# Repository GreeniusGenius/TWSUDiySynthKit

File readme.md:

# About

- This product is borne out of an original synthesiser kit built by the now bankrupt [Tech Will Save Us](https://en.wikipedia.org/wiki/Technology_Will_Save_Us) company.
- The solderless breadboard nature of it frustrated me, and the lack of room to add a microcontroller for MIDI functionality on the breadboard made it unusable for how I would wish to use it.
- Then I got bored whilst designing it, and decided I'd turn it into a Pi Pico (2(W)) dev board too.
- That way I can prototype all of my projects in a single multipurpose board.
- It supports a Raspberry Pi standard hat.
- It supports a Raspberry Pi Pico bonnet.
- _The second Pi you see in the renderings is actually where two headers will go allowing bonnets to be attached like eInk displays_
- It supports Adafruit Stemma QT and Stemma connectors - which are perfect for prototyping using breakout boards due to the reliable solderless connections.
- It lets me try out the usage of jumpers to bypass voltage dividers reducing potential PCB revisions required due to calculation errors.

_The PCB is a cost-effective two layer design with ground pours and high density of via stitching reduce ground loops and EMI._

_Plated and grounded mounting holes are used to allow easy multimeter probing and increase durability._

_The case shields the synthesiser board and Pi Pico (2(W)) whilst the bonnet, hat, and JST connectors for peripherals are easily accessible_

## Bill of Materials
| Reference | Qty | Value                                             | Datasheet                                                                                                                                                                                                                                                                                                                                                                                                                                                                      | Link / URL                                                                                                     | Manufacturer  | Manufacturer_Part_Number | Price (GBP) | GBP/USD              | Price (USD) | Justification                                                                                            |
| --------- | --- | ------------------------------------------------- | ------------------------------------------------------------------------------------------------------------------------------------------------------------------------------------------------------------------------------------------------------------------------------------------------------------------------------------------------------------------------------------------------------------------------------------------------------------------------------ | -------------------------------------------------------------------------------------------------------------- | ------------- | ------------------------ | ----------- | -------------------- | ----------- | -------------------------------------------------------------------------------------------------------- |
| R1, R2    | 2   | 2k 16mm Potentiometer                             | [https://static.rapidonline.com/pdf/65-1480.pdf](https://static.rapidonline.com/pdf/65-1480.pdf)                                                                                                                                                                                                                                                                                                                                                                               | https://www.rapidonline.com/omeg-eco2k2lin-2k2-linear-single-16mm-control-pot-65-1401                          | Omeg          | ECO2K2LIN                | £1.75       |  $              1.36 | USD 2.38    | For the volume control and adjustment of the midi volume too                                             |
| R3, R6    | 2   | 470k 16mm potentiometer                           | [https://static.rapidonline.com/pdf/65-1400e.pdf](https://static.rapidonline.com/pdf/65-1400e.pdf)                                                                                                                                                                                                                                                                                                                                                                             | https://www.rapidonline.com/omeg-ecoswx470klin-470k-eco-16mm-linear-switched-control-65-1494                   | Omeg          | ECOSWX470KLIN            | £2.57       |  $              1.36 | USD 3.49    | For the input for the synthesizer                                                                        |
| J6        | 1   | JST XH p2.54mm 4 pin 20cm long wire and connector | [https://www.aliexpress.com/item/1005007460897865.html#nav-specification](https://www.aliexpress.com/item/1005007460897865.html#nav-specification)                                                                                                                                                                                                                                                                                                                             | [https://www.aliexpress.com/item/1005007460897865.html](https://www.aliexpress.com/item/1005007460897865.html) | Generic       | ~                        | £0.75       |  $              1.36 | USD 1.02    | Cables for the PCB mount JST connectors to attach accessories                                            |
| J8        | 1   |  JST SH 1.0mm 4 pin 300mm wire and conenctor      | https://www.aliexpress.com/item/1005007218127653.html?spm=a2g0o.productlist.main.1.63d76305UmTvS8&algo_pvid=8017bda6-71a1-4b7b-932a-028b233ec6b2&algo_exp_id=8017bda6-71a1-4b7b-932a-028b233ec6b2-0&pdp_ext_f=%7B%22order%22%3A%221971%22%2C%22eval%22%3A%221%22%7D&pdp_npi=4%40dis%21GBP%210.59%210.59%21%21%215.53%215.53%21%40210390c917491563321605448e615d%2112000039871029577%21sea%21UK%210%21ABX&curPageLogUid=Gzq5NMQj9i6H&utparam-url=scene%3Asearch%7Cquery_from%3A | https://www.aliexpress.com/item/1005007218127653.html                                                          | Generic       | ~                        | £0.81       |  $              1.36 | USD 2.21    |                                                                                                          |
| J7        | 1   | JST PH 2.0mm 4 pin connector                      | https://www.aliexpress.com/item/32959854422.html#nav-description                                                                                                                                                                                                                                                                                                                                                                                                               | https://www.aliexpress.com/item/32959854422.html                                                               | Generic       | ~                        | £1.63       |  $              1.36 | USD 1.91    |                                                                                                          |
| J8        | 2   | JST PH 2.0mm 3 pin connector                      | https://www.aliexpress.com/item/32959854422.html#nav-description                                                                                                                                                                                                                                                                                                                                                                                                               | https://www.aliexpress.com/item/32959854422.html                                                               | Generic       | ~                        | £1.41       |  $              1.36 | USD 1.91    |                                                                                                          |
| J2        | 1   | JST XH p2.54mm 2 pin 20cm long wire and connector | [https://www.aliexpress.com/item/1005007460897865.html#nav-specification](https://www.aliexpress.com/item/1005007460897865.html#nav-specification)                                                                                                                                                                                                                                                                                                                             | [https://www.aliexpress.com/item/1005007460897865.html](https://www.aliexpress.com/item/1005007460897865.html) | Generic       | ~                        | £0.75       |  $              1.36 | USD 1.02    |                                                                                                          |
| J6        | 1   | 16mm 3V LED Button                                | [https://www.aliexpress.com/item/1005008024309525.html#nav-specification](https://www.aliexpress.com/item/1005008024309525.html#nav-specification)                                                                                                                                                                                                                                                                                                                             | https://www.aliexpress.com/item/1005008024309525.html                                                          | Generic       | ~                        | £1.26       |  $              1.36 | USD 1.71    | Push to pair bluetooth                                                                                   |
|           |     | USB-A to Micro-USB cable 0.9m                     | https://www.amazon.co.uk/dp/B0711PVX6Z?th=1                                                                                                                                                                                                                                                                                                                                                                                                                                    | https://www.amazon.co.uk/dp/B0711PVX6Z                                                                         | Amazon Basics | ~                        | £3.16       |  $              1.36 | USD 4.29    | Genuinely run out of Micro USB cables - happy to find a cheaper one if necessary as long as it does data |
| PCB       | 1   | 5 PCBs (minimum JLCPCB order)                     | ~                                                                                                                                                                                                                                                                                                                                                                                                                                                                              | jlcpcb.com                                                                                                     | JLCPCB        | ~                        | £23.35      |  $              1.36 | USD 31.71   | The PCB                                                                                                  |
|           |     |                                                   |                                                                                                                                                                                                                                                                                                                                                                                                                                                                                |                                                                                                                |               |                          |             |                      |             |                                                                                                          |
|           |     |                                                   |                                                                                                                                                                                                                                                                                                                                                                                                                                                                                |                                                                                                                |               |                          |             |                      |             |                                                                                                          |
|           |     |                                                   |                                                                                                                                                                                                                                                                                                                                                                                                                                                                                |                                                                                                                |               |                          |             |                      |             |                                                                                                          |
|           |     |                                                   |                                                                                                                                                                                                                                                                                                                                                                                                                                                                                |                                                                                                                |               | Total Price              | £37.44      |                      | USD 51.65   |                                                                                                          |
| **Reference**                    | **Qty** | **Value**                    | **DNP** | **Exclude from BOM** | **Exclude from Board** | **Footprint**                                                    | **Datasheet**                                                                                                                                                                                                                                                                  | **JLCPCB ID** | **Manufacturer**                      | **Manufacturer_Part_Number** | **Mouser Part Number** |
| -------------------------------- | ------- | ---------------------------- | ------- | -------------------- | ---------------------- | ---------------------------------------------------------------- | ------------------------------------------------------------------------------------------------------------------------------------------------------------------------------------------------------------------------------------------------------------------------------ | ------------- | ------------------------------------- | ---------------------------- | ---------------------- |
| **R5**                           | 1       | 2k_0603                      |         |                      |                        | PCM_Resistor_SMD_AKL:R_0603_1608Metric_Pad0.98x0.95mm_HandSolder | [https://www.vishay.com/doc?60018](https://www.vishay.com/doc?60018)                                                                                                                                                                                                           | C2076992      | Vishay                                | M55342E12B2B00RT5            | 75-M55342E12B2B00RT5   |
| **R8,R9**                        | 2       | 10k_0603                     |         |                      |                        | PCM_Resistor_SMD_AKL:R_0603_1608Metric_Pad0.98x0.95mm_HandSolder | [https://www.vishay.com/doc?28758](https://www.vishay.com/doc?28758)                                                                                                                                                                                                           | C2130614      | Vishay                                | TNPW060310K0FHEA             | 71-TNPW060310K0FHEA    |
| **R4,R7**                        | 2       | 1k_0603                      |         |                      |                        | PCM_Resistor_SMD_AKL:R_0603_1608Metric_Pad1.05x0.95mm_HandSolder | [https://www.mouser.co.uk/datasheet/2/385/SEI_RMCF_RMCP-3077565.pdf](https://www.mouser.co.uk/datasheet/2/385/SEI_RMCF_RMCP-3077565.pdf)                                                                                                                                       | C4130738      | SEI Stackpole                         | RMCF0603JG1K00               | 708-RMCF0603JG1K00     |
| **R13**                          | 1       | 1k_1210                      |         |                      |                        | PCM_Resistor_SMD_AKL:R_0603_1608Metric_Pad1.05x0.95mm_HandSolder | [https://4donline.ihs.com/images/VipMasterIC/IC/PANA/PANA-S-A0012789169/PANA-S-A0012789169-1.pdf?hkey=CECEF36DEECDED6468708AAF2E19C0C6](https://4donline.ihs.com/images/VipMasterIC/IC/PANA/PANA-S-A0012789169/PANA-S-A0012789169-1.pdf?hkey=CECEF36DEECDED6468708AAF2E19C0C6) | C20024203     | Yageo                                 | ERJ-T14LK102U                | 667-ERJ-T14LK102U      |
| **C7**                           | 1       | 10uf Electrolytic Capacitor  |         |                      |                        | PCM_Capacitor_THT_AKL:CP_Radial_D6.3mm_P2.50mm                   | [https://industrial.panasonic.com/cdbs/www-data/pdf/RDF0000/ABA0000C1059.pdf](https://industrial.panasonic.com/cdbs/www-data/pdf/RDF0000/ABA0000C1059.pdf)                                                                                                                     | C1583769      | Panasonic                             | ECE-A1HKS100B                | 667-ECE-A1HKS100B      |
| **R12**                          | 1       | 68R_1210                     |         |                      |                        | PCM_Resistor_SMD_AKL:R_0603_1608Metric_Pad1.05x0.95mm_HandSolder | [https://www.mouser.co.uk/datasheet/2/447/PYu_AC_51_RoHS_L_11-3418659.pdf](https://www.mouser.co.uk/datasheet/2/447/PYu_AC_51_RoHS_L_11-3418659.pdf)                                                                                                                           | C230487       | Yageo                                 | AC1210JR-0768RL              | 603-AC1210JR-0768RL    |
| **U1**                           | 1       | NE556                        |         |                      |                        | Package_DIP:DIP-14_W7.62mm_Socket_LongPads                       | [http://www.ti.com/lit/ds/symlink/ne556.pdf](http://www.ti.com/lit/ds/symlink/ne556.pdf)                                                                                                                                                                                       | C66175        | Texas Instruments                     | NE556N                       | 595-NE556N             |
| **A1**                           | 1       | RaspberryPi_Pico_2W          |         |                      |                        | Module_RaspberryPi_Pico:RaspberryPi_Pico_W_SMD                   | [https://datasheets.raspberrypi.com/picow/pico-2-w-datasheet.pdf](https://datasheets.raspberrypi.com/picow/pico-2-w-datasheet.pdf)                                                                                                                                             |               | Raspberry Pi Foundation               | SC1633                       | 358-SC1633             |
| **J8**                           | 1       | Conn_01x04_Socket            |         |                      |                        | Connector_JST:JST_SH_SM04B-SRSS-TB_1x04-1MP_P1.00mm_Horizontal   | [https://www.mouser.co.uk/datasheet/2/564/eGH-3477624.pdf](https://www.mouser.co.uk/datasheet/2/564/eGH-3477624.pdf)                                                                                                                                                           | C7279904      | Japan Solderless Terminals            | SM04B-GHMG-TB-(LF)(SN)       | 306-SM04BGHMGTBLFSN    |
| **J6**                           | 1       | Conn_01x04_Socket            |         |                      |                        | Connector_JST:JST_XH_S4B-XH-A-1_1x04_P2.50mm_Horizontal          | [https://www.mouser.co.uk/datasheet/2/564/eXH-3476786.pdf](https://www.mouser.co.uk/datasheet/2/564/eXH-3476786.pdf)                                                                                                                                                           | C163037       | Japan Solderless Terminals            | S4B-XH-A-1(LF)(SN)           | 306-S4BXHA1LFSN        |
| **R3,R6**                        | 2       | ECO2K2LIN                    |         |                      |                        | Connector_JST:JST_XH_S3B-XH-A-1_1x03_P2.50mm_Horizontal          | [https://static.rapidonline.com/pdf/65-1400e.pdf](https://static.rapidonline.com/pdf/65-1400e.pdf), [https://www.mouser.co.uk/datasheet/2/564/eXH-3476786.pdf](https://www.mouser.co.uk/datasheet/2/564/eXH-3476786.pdf)                                                       | C163036       | Japan Solderless Terminals            | S3B-XH-A-1(LF)(SN)           | 306-S3BXHA1LFSN        |
| **R1,R2**                        | 2       | ECOSWX470KLIN                |         |                      |                        | Connector_JST:JST_XH_S3B-XH-A-1_1x03_P2.50mm_Horizontal          | [https://static.rapidonline.com/pdf/65-1494.pdf](https://static.rapidonline.com/pdf/65-1494.pdf), [https://www.mouser.co.uk/datasheet/2/564/eXH-3476786.pdf](https://www.mouser.co.uk/datasheet/2/564/eXH-3476786.pdf)                                                         | C163036       | Japan Solderless Terminals            | S3B-XH-A-1(LF)(SN)           | 306-S3BXHA1LFSN        |
| **J7**                           | 1       | Conn_01x04_Socket            |         |                      |                        | Connector_JST:JST_PH_S4B-PH-K_1x04_P2.00mm_Horizontal            | [https://www.mouser.co.uk/datasheet/2/564/JST_B4B_PH_SM4_TB_LF_SN_ePH-3481264.pdf](https://www.mouser.co.uk/datasheet/2/564/JST_B4B_PH_SM4_TB_LF_SN_ePH-3481264.pdf)                                                                                                           | C157926       | Japan Solderless Terminals            | S4B-PH-K-S(LF)(SN)           | 306-S4BPHKSLFSN        |
| **J9,J10**                       | 2       | Conn_01x03_Socket            |         |                      |                        | Connector_JST:JST_PH_S3B-PH-K_1x03_P2.00mm_Horizontal            | [https://www.mouser.co.uk/datasheet/2/564/JST_B4B_PH_SM4_TB_LF_SN_ePH-3481264.pdf](https://www.mouser.co.uk/datasheet/2/564/JST_B4B_PH_SM4_TB_LF_SN_ePH-3481264.pdf)                                                                                                           | C157929       | Japan Solderless Terminals Commercial | S3B-PH-K-S(LF)(SN)           | 306-S3BPHKSLFSN        |
| **J2**                           | 1       | Conn_01x02                   |         |                      |                        | Connector_JST:JST_XH_S2B-XH-A-1_1x02_P2.50mm_Horizontal          | [https://www.mouser.co.uk/datasheet/2/564/eXH-3476786.pdf](https://www.mouser.co.uk/datasheet/2/564/eXH-3476786.pdf)                                                                                                                                                           | C157931       | Japan Solderless Terminals            | S2B-XH-A(LF)(SN)             | 306-S2B-XH-ALFSN       |
| **C4,C5,C6**                     | 3       | 0.1uF_0603_16V               |         |                      |                        | Capacitor_SMD:C_1206_3216Metric_Pad1.33x1.80mm_HandSolder        | [https://www.mouser.co.uk/datasheet/2/585/MLCC-1837944.pdf](https://www.mouser.co.uk/datasheet/2/585/MLCC-1837944.pdf)                                                                                                                                                         | C6766062      | Samsung Electro-Mechanics             | CL31B104KBCNNND              | 187-CL31B104KBCNNND    |
| **C1,C3,C9,C10,C11,C12,C13,C14** | 8       | 0.1uF                        |         |                      |                        | Capacitor_SMD:C_1206_3216Metric_Pad1.33x1.80mm_HandSolder        | [https://www.mouser.co.uk/datasheet/2/585/MLCC-1837944.pdf](https://www.mouser.co.uk/datasheet/2/585/MLCC-1837944.pdf)                                                                                                                                                         | C6766062      | Samsung Electro-Mechanics             | CL31B104KBCNNND              | 187-CL31B104KBCNNND    |
| **C2,C8**                        | 2       | 10nF_0603_25V                |         |                      |                        | Capacitor_SMD:C_1206_3216Metric_Pad1.33x1.80mm_HandSolder        | [https://www.mouser.co.uk/datasheet/2/585/MLCC-1837944.pdf](https://www.mouser.co.uk/datasheet/2/585/MLCC-1837944.pdf)                                                                                                                                                         | C16196152     | Samsung Electro-Mechanics             | CL31B103KHFNFNE              | 187-CL31B103KHFNFNE    |
| **TP1,TP2**                      | 2       | TestPoint                    |         |                      |                        | TestPoint:TestPoint_Pad_D2.5mm                                   | ~                                                                                                                                                                                                                                                                              |               |                                       |                              |                        |
| **NT1,NT2,NT3**                  | 3       | NetTie_2                     |         | Excluded from BOM    |                        | NetTie:NetTie-2_SMD_Pad0.5mm                                     | ~                                                                                                                                                                                                                                                                              |               |                                       |                              |                        |
| **J14**                          | 1       | Conn_01x04_Socket            |         |                      |                        | Connector_PinSocket_2.54mm:PinSocket_1x04_P2.54mm_Vertical       | ~                                                                                                                                                                                                                                                                              |               |                                       |                              |                        |
| **J11,J12**                      | 2       | Conn_01x03_Socket            |         |                      |                        | Connector_PinSocket_2.54mm:PinSocket_1x03_P2.54mm_Vertical       | ~                                                                                                                                                                                                                                                                              |               |                                       |                              |                        |
| **J5**                           | 1       | Raspberry_Pi_2x20_PTH        |         |                      |                        | Connector_PinHeader_2.54mm:PinHeader_2x20_P2.54mm_Vertical       | [https://www.raspberrypi.org/documentation/hardware/raspberrypi/schematics/rpi_SCH_3bplus_1p0_reduced.pdf](https://www.raspberrypi.org/documentation/hardware/raspberrypi/schematics/rpi_SCH_3bplus_1p0_reduced.pdf)                                                           |               |                                       |                              |                        |
| **J3,J4**                        | 2       | Conn_01x07_Pin               |         |                      |                        | Connector_PinSocket_2.54mm:PinSocket_1x07_P2.54mm_Horizontal     | ~                                                                                                                                                                                                                                                                              |               |                                       |                              |                        |
| **J1**                           | 1       | Conn_02x02_Counter_Clockwise |         |                      |                        | Connector_PinSocket_2.54mm:PinSocket_2x02_P2.54mm_Horizontal     | ~                                                                                                                                                                                                                                                                              |               |                                       |                              |                        |
| **H5,H6,H7,H8,H9,H10,H11,H12**   | 8       | MountingHole_Pad             |         | Excluded from BOM    |                        | MountingHole:MountingHole_2.7mm_M2.5_DIN965_Pad                  | ~                                                                                                                                                                                                                                                                              |               |                                       |                              |                        |
| **H1,H2,H3,H4**                  | 4       | MountingHole_Pad             |         | Excluded from BOM    |                        | MountingHole:MountingHole_2.2mm_M2_DIN965                        | ~                                                                                                                                                                                                                                                                              |               |                                       |                              |                        |
| **A2**                           | 1       | RaspberryPi_Pico_W           |         | Excluded from BOM    |                        | Module_RaspberryPi_Pico:RaspberryPi_Pico_Common_MountingHoles    | [https://datasheets.raspberrypi.com/picow/pico-w-datasheet.pdf](https://datasheets.raspberrypi.com/picow/pico-w-datasheet.pdf)                                                                                                                                                 |               |                                       |                              |                        |

| FileName                   | Quantity | Price  |
|----------------------------|----------|--------|
| InitialBaseBoard Base.step | 1        | $17.16 |
| InitialBaseBoard Lid.step  | 1        | $7.78  |

Notes: The .csv file contains the PCB mounted bill of materials.
The ExtraBOM contains the wiring needed to connect etc.
The link to the mouser basket is here: https://www.mouser.co.uk/ProjectManager/ProjectDetail.aspx?AccessID=711d47ef2e

Mouser components + shipping to United Kingdom is £24.41 or US$33.12

Components in .xlsx are £43.17 or US$59.46

3D Printed Casing is about US$24.94 (£18.41) + at least US$16.10 (£11.88) shipping from PCBWay for a total of £30.29 and US$41.04

**Therefore the total cost is £97.87 and US$133.62.**

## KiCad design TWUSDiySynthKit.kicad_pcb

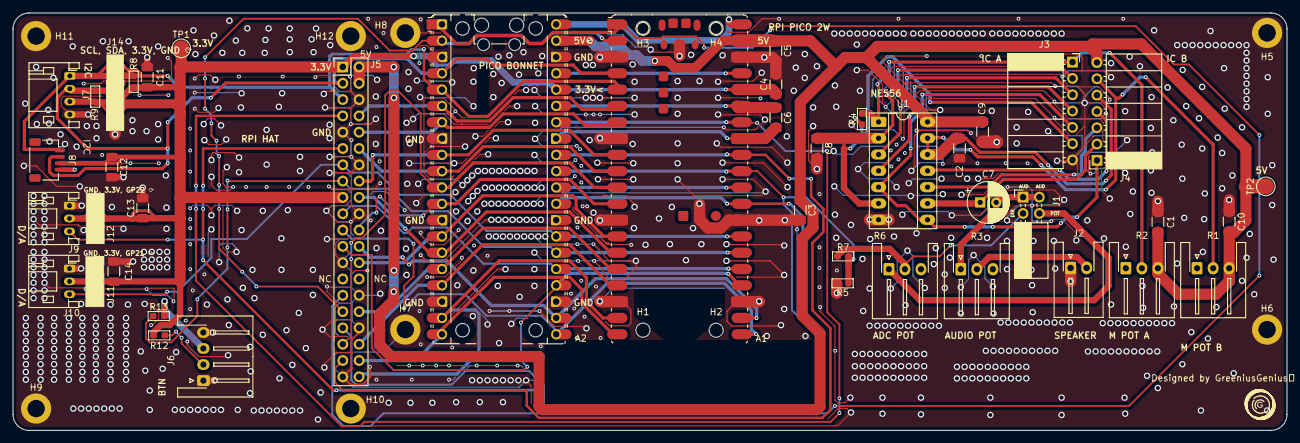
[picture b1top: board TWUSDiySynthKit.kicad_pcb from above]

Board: 2 copper layers, 198.4 x 65.0 mm, 58 parts (0 on the bottom side), 52 nets.

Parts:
A1: RaspberryPi_Pico_W; RaspberryPi_Pico_W_SMD
A2: RaspberryPi_Pico_W; RaspberryPi_Pico_Common_MountingHoles
C1, C3, C9, C10, C11, C12, C13, C14: 0.1uF; C_1206_3216Metric_Pad1.33x1.80mm_HandSolder
C2, C8: 10nF_0603_25V; C_1206_3216Metric_Pad1.33x1.80mm_HandSolder
C4, C5, C6: 0.1uF_0603_16V; C_1206_3216Metric_Pad1.33x1.80mm_HandSolder
C7: 10uf Electrolytic Capacitor; CP_Radial_D6.3mm_P2.50mm
H1, H2, H3, H4: MountingHole_Pad; MountingHole_2.2mm_M2_DIN965
H5, H6, H7, H8, H9, H10, H11, H12: MountingHole_Pad; MountingHole_2.7mm_M2.5_DIN965_Pad
J1: Conn_02x02_Counter_Clockwise; PinSocket_2x02_P2.54mm_Horizontal
J2: Conn_01x02; JST_XH_S2B-XH-A-1_1x02_P2.50mm_Horizontal
J3, J4: Conn_01x07_Pin; PinSocket_1x07_P2.54mm_Horizontal
J5: Raspberry_Pi_2x20_PTH; PinHeader_2x20_P2.54mm_Vertical
J6: Conn_01x04_Socket; JST_XH_S4B-XH-A-1_1x04_P2.50mm_Horizontal
J7: Conn_01x04_Socket; JST_PH_S4B-PH-K_1x04_P2.00mm_Horizontal
J8: Conn_01x04_Socket; JST_SH_SM04B-SRSS-TB_1x04-1MP_P1.00mm_Horizontal
J9, J10: Conn_01x03_Socket; JST_PH_S3B-PH-K_1x03_P2.00mm_Horizontal
J11, J12: Conn_01x03_Socket; PinSocket_1x03_P2.54mm_Vertical
J14: Conn_01x04_Socket; PinSocket_1x04_P2.54mm_Vertical
NT1, NT2, NT3: NetTie_2; NetTie-2_SMD_Pad0.5mm
R1, R2: ECOSWX470KLIN; JST_XH_S3B-XH-A-1_1x03_P2.50mm_Horizontal
R3, R6: ECO2K2LIN; JST_XH_S3B-XH-A-1_1x03_P2.50mm_Horizontal
R4, R7: 1k_0603; R_0603_1608Metric_Pad1.05x0.95mm_HandSolder
R5: 2k_0603; R_0603_1608Metric_Pad0.98x0.95mm_HandSolder
R8, R9: 10k_0603; R_0603_1608Metric_Pad0.98x0.95mm_HandSolder
R12: 68R_1210; R_0603_1608Metric_Pad1.05x0.95mm_HandSolder
R13: 1k_1210; R_0603_1608Metric_Pad1.05x0.95mm_HandSolder
TP1, TP2: TestPoint; TestPoint_Pad_D2.5mm
U1: NE556; DIP-14_W7.62mm_Socket_LongPads

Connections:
1DIS: J3.1, R2.2 (Wiper), R4.2, U1.1 (DIS)
2THR: C8.1, J3.2, NT2.1, U1.2 (THR)
3CV: J3.3, U1.3 (CV)
4RST: J3.4, U1.4 (R)
5OUT: J3.5, NT3.1, U1.5 (Q)
5V: A1.39 (VSYS), A2.39 (VSYS), C1.1, C3.1, C5.1, C9.1, C10.1, J4.14, J5.2 (5V), J5.4 (5V), R1.3, R2.3, TP2.1, U1.14 (VCC)
6TRIG: J3.6, NT2.2, R4.1, U1.6 (TR)
8TRIG: J4.8, NT3.2, U1.8 (TR)
9OUT: C7.1, J4.9, U1.9 (Q)
10RST: J4.10, U1.10 (R)
11CV: J4.11, U1.11 (CV)
12THR: C2.1, J4.12, NT1.1, U1.12 (THR)
13DIS: J4.13, NT1.2, R1.2 (Wiper), U1.13 (DIS)
+3.3V: A1.36 (3V3), A2.36 (3V3), C4.1, C11.1, C12.1, C13.1, C14.1, J5.1 (3V3), J5.17 (3V3), J7.3, J8.3, J9.2, J10.2, J11.2, J12.2, J14.3, R8.2, R9.2, R12.1, TP1.1
GND: A1.3 (GND), A1.8 (GND), A1.13 (GND), A1.18 (GND), A1.23 (GND), A1.28 (GND), A1.38 (GND), A1.D2 (GND), A1.TP1 (USB_GND), A2.3 (GND), A2.8 (GND), A2.13 (GND), A2.18 (GND), A2.23 (GND), A2.28 (GND), A2.38 (GND), C1.2, C2.2, C3.2, C4.2, C5.2, C8.2, C9.2, C10.2, C11.2, C12.2, C13.2, C14.2, H5.1, H6.1, H7.1, H8.1, H9.1, H10.1, H11.1, H12.1, J2.1, J3.7, J5.6 (GND), J5.9 (GND), J5.14 (GND), J5.20 (GND), J5.25 (GND), J5.30 (GND), J5.34 (GND), J5.39 (GND), J6.1, J6.4, J7.4, J8.4, J9.1, J10.1, J11.1, J12.1, J14.4, R5.2, U1.7 (GND)
unnamed: A1.37 (3V3_EN), A2.37 (3V3_EN)
unnamed: A1.35 (ADC_VREF), A2.35 (ADC_VREF), C6.1
unnamed: A1.33 (AGND), A2.33 (AGND), C6.2
unnamed: A1.1 (GPIO0), A2.1 (GPIO0), J5.29 (GCLK1/GPIO5)
unnamed: A1.2 (GPIO1), A2.2 (GPIO1), J5.31 (GCLK2/GPIO6)
unnamed: A1.4 (GPIO2), A2.4 (GPIO2), J5.3 (SDA/GPIO2), J7.2, J8.2, J14.2, R9.1
unnamed: A1.5 (GPIO3), A2.5 (GPIO3), J5.5 (SCL/GPIO3), J7.1, J8.1, J14.1, R8.1
unnamed: A1.6 (GPIO4), A2.6 (GPIO4), J5.8 (GPIO14/TXD)
unnamed: A1.7 (GPIO5), A2.7 (GPIO5), J5.10 (GPIO15/RXD)
unnamed: A1.9 (GPIO6), A2.9 (GPIO6), J5.16 (GPIO23)
unnamed: A1.10 (GPIO7), A2.10 (GPIO7), J5.12 (GPIO18/PWM0)
unnamed: A1.11 (GPIO8), A2.11 (GPIO8), J5.35 (GPIO19/POCI1)
unnamed: A1.12 (GPIO9), A2.12 (GPIO9), J5.22 (GPIO25)
unnamed: A1.14 (GPIO10), A2.14 (GPIO10), J5.26 (~CE1/GPIO7)
unnamed: A1.15 (GPIO11), A2.15 (GPIO11), J5.18 (GPIO24)
unnamed: A1.16 (GPIO12), A2.16 (GPIO12), J5.32 (PWM0/GPIO12)
unnamed: A1.17 (GPIO13), A2.17 (GPIO13), J5.36 (GPIO16)
unnamed: A1.19 (GPIO14), A2.19 (GPIO14), J5.40 (GPIO21/SCLK1)
unnamed: A1.20 (GPIO15), A2.20 (GPIO15), J5.38 (GPIO20/PICO1)
unnamed: A1.21 (GPIO16), A2.21 (GPIO16), J5.21 (POCI0/GPIO9)
unnamed: A1.22 (GPIO17), A2.22 (GPIO17), J5.24 (~CE0/GPIO8)
unnamed: A1.24 (GPIO18), A2.24 (GPIO18), J5.23 (SCLK0/GPIO11)
unnamed: A1.25 (GPIO19), A2.25 (GPIO19), J5.19 (PICO0/GPIO10)
unnamed: A1.26 (GPIO20), A2.26 (GPIO20), J5.15 (GPIO22), R13.1
unnamed: A1.27 (GPIO21), A2.27 (GPIO21), J5.13 (GPIO27), J10.3, J11.3
unnamed: A1.29 (GPIO22), A2.29 (GPIO22), J5.11 (GPIO17), J9.3, J12.3
unnamed: A1.32 (GPIO27_ADC1), A2.32 (GPIO27_ADC1), J5.37 (GPIO26)
unnamed: A1.34 (GPIO28_ADC2), A2.34 (GPIO28_ADC2), J5.7 (GCLK0/GPIO4)
unnamed: A1.30 (RUN), A2.30 (RUN)
unnamed: A1.40 (VBUS), A2.40 (VBUS)
unnamed: C7.2, J1.1, J1.3, R3.1
unnamed: J1.2, R6.2 (Wiper), R7.1
unnamed: J1.4, R6.1
unnamed: J2.2, R3.2 (Wiper)
unnamed: J6.2, R12.2
unnamed: J6.3, R13.2
OUTPUTB_ADC: A1.31 (GPIO26_ADC0), A2.31 (GPIO26_ADC0), J5.33 (PWM1/GPIO13), R5.1, R7.2

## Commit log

2025-06-02 Added p2.54mm dupont headers as alternative for Stemma JST connectors
2025-06-02 Added further guarding traces to reduce EMI, optimised vias etc. etc.
2025-06-02 Labelled test pads
2025-06-05 Export using correct tool
2025-06-05 attempt to round
2025-06-05 Improve ground stitching
2025-06-05 Added bill of materials
2025-06-05 Create TWSUSynthKitFirmware
2025-06-05 Stuff
2025-06-05 Updated 3D model etc
2025-06-05 Added 3d renders
2025-06-05 Added stuff
2025-06-05 Added PDF file of pcb and schematic
2025-06-05 Added images, interactive BOM, journal etc.
2025-06-05 Added logo
2025-06-06 more images
2025-06-06 Updated BOM to account for quantity, added 3D renders and stuff
2025-06-06 Added latest cad files
2025-06-06 removed older fusion 360 file
2025-06-06 Added latest cad models with threading and update readme
2025-06-06 Replaced images with ray traced with latest silkscreening
2025-06-06 Updated journal with images
2025-06-06 Added speaker aperture
2025-06-11 widened gnd traces and connected missing gpio trace
2025-06-14 Amend lid mounting screw placement
